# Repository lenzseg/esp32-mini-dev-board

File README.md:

# ESP32-C3 Mini Dev Board

Compact 4-layer ESP32-C3 development board with native USB-C, a 3.3 V LDO, USB ESD/surge protection and breakout headers, designed in KiCad 10 and prepared for JLCPCB fabrication.

## Overview

A small, low-cost breadboard-friendly board for prototyping with the ESP32-C3 (Wi-Fi + BLE, RISC-V). It is a personal design project that covers the full hardware flow: schematic capture, a custom component library with manufacturer part numbers, 4-layer layout with controlled-impedance USB routing, DFM checks and fabrication outputs.

**Design goals**
- Power and program the board over a single USB-C cable (native USB, no USB-UART bridge)
- Protect the USB port against ESD and surge events
- Keep the board small, with the module antenna kept clear of copper
- Use parts that are in stock at the assembly house and pass the fab's DFM rules

## Key specifications

| Item | Value |
|---|---|
| Module | ESP32-C3-WROOM-02 |
| Input power | 5 V via USB-C (also on the 5V header pin) |
| 3.3 V regulator | AP2112K-3.3 LDO |
| USB protection | USBLC6-2SC6 (ESD on data lines), SMAJ5.0A TVS (VBUS) |
| Clocks | 32.768 kHz crystal (FC-135R) for the RTC |
| User controls | BOOT and RST (EN) push buttons |
| Headers | 2 × 8-pin, 2.54 mm (power, UART, GPIO) |
| Board size | 30.6 × 38.0 mm |
| Layers / thickness | 4 layers, 1.6 mm (1.5842 mm calculated stackup) |
| USB differential pair | 90 Ω target, 0.1925 mm trace / 0.18 mm gap (USB net class) |
| EDA | KiCad 10 |
| Revision | 1.0 |

## Design highlights

- **Power entry:** USB-C VBUS passes through a surge TVS (SMAJ5.0A) before the AP2112K-3.3 LDO. Bulk and bypass capacitors (4.7 µF, GRM188Z71C475KE21D) are placed at the regulator and module supply pins.
- **USB protection:** USBLC6-2SC6 on D+/D- for low-capacitance ESD protection, placed close to the connector.
- **Controlled-impedance USB:** D+/D- are routed as a 90 Ω differential pair on the top layer over a solid GND plane (see [PCB layout](#pcb-layout)).
- **Antenna keep-out:** the module's antenna overhangs the board edge, with no copper or components under it.
- **Boot and reset:** BOOT (GPIO9) and EN push buttons with pull-ups and debounce capacitors allow programming without external tools.
- **Manufacturability:** the layout was revised to pass the JLCDFM checks. Copper zones were resized, vias were removed from silkscreen, keep-outs were added around the soldermask-expansion rule bug, headers were moved away from the module to satisfy the THT-SMT spacing rule, and track spacing was increased.
- **Own component library:** symbols in `libs/` carry an IPN and MPN for each part, so the BOM is traceable.

## Pinout

Header pin labels follow the board silkscreen (see the render above). Check them against the schematic before wiring anything.

| Header | Pins (square pad first) |
|---|---|
| Left | 3V3, GND, EN, 4, 5, 6, 7, BOOT |
| Right | 5V, GND, 3, GND, TX, RX, GND, 10 |

Numbers are ESP32-C3 GPIO numbers.

## Schematics

Source files are in [`src/`](src):

- `esp32-mini-dev-board.kicad_sch`: root sheet and index
- `block-diagram.kicad_sch`: system block diagram
- `circuit-design.kicad_sch`: detailed circuit (USB power entry, 3.3 V LDO, module, clock, BOOT/EN, headers)

## PCB layout

| Top | Inner 1 (GND) | Inner 2 (power) | Bottom (mirrored) |
|---|---|---|---|
|  |  |  |  |

## Tools

- KiCad 10.0
- KiCad PCB Calculator (coupled microstrip) for the differential-pair impedance

## Author

Nelson Rodriguez (LENZSEG)

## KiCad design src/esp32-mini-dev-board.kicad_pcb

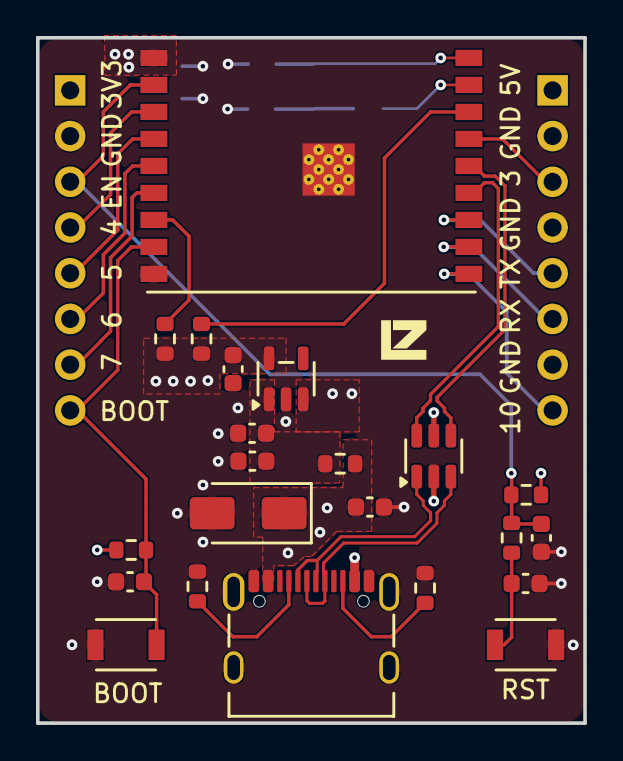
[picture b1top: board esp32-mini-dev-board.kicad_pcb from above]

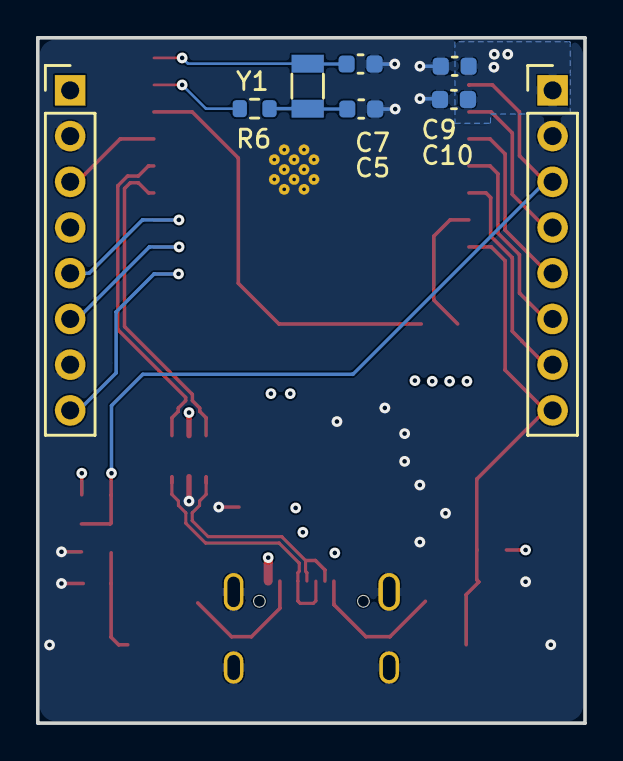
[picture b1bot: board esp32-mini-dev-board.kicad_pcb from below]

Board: 4 copper layers, 30.4 x 38.1 mm, 30 parts (8 on the bottom side), 26 nets.

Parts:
C1, C2, C3, C4, C6, C8, C9, C11: 4.7uF; C_0603_1608Metric
C5, C7, C10: C; C_0603_1608Metric
D1: SMAJ5.0A; D_SMA
J1: USB_C_Receptacle_USB2.0_16P; USB_C_Receptacle_G-Switch_GT-USB-7010ASV
J2, J3: Conn_01x08_Pin; PinHeader_1x08_P2.54mm_Vertical
R1, R2, R3, R4, R5, R6, R7, R8, R9: R; R_0603_1608Metric
SW1, SW2: SW_Push; SW_SPST_B3U-1000P
U1: USBLC6-2SC6; SOT-23-6
U2: AP2112K-3.3; SOT-23-5
U3: ESP32-C3-WROOM-02
Y1: 32.768kHz; Crystal_SMD_3215-2Pin_3.2x1.5mm

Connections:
+3V3: C8.1, C9.1, C10.1, J2.1, R4.1, R7.1, R8.1, R9.1, U2.5 (VOUT), U3.1 (3V3)
+5V: C4.1, C6.1, J3.1, R5.2, U2.1 (VIN), U2.3 (EN)
/CIRCUIT DESIGN/BOOT: C11.1, J2.8, R9.2, SW2.2, U3.8 (IO9)
/CIRCUIT DESIGN/EN: C3.1, J2.3, R3.2, R4.2, U3.2 (EN)
/CIRCUIT DESIGN/IO3: J3.3, U3.15 (IO3)
/CIRCUIT DESIGN/IO4: J2.4, U3.3 (IO4)
/CIRCUIT DESIGN/IO5: J2.5, U3.4 (IO5)
/CIRCUIT DESIGN/IO6: J2.6, U3.5 (IO6)
/CIRCUIT DESIGN/IO7: J2.7, U3.6 (IO7)
/CIRCUIT DESIGN/IO10: J3.8, U3.10 (IO10)
/CIRCUIT DESIGN/RXD: J3.6, U3.11 (IO20/RXD)
/CIRCUIT DESIGN/TXD: J3.5, U3.12 (IO21/TXD)
/CIRCUIT DESIGN/USB_D+: U1.4 (I/O2), U3.14 (IO19)
/CIRCUIT DESIGN/USB_D-: U1.6 (I/O1), U3.13 (IO18)
/CIRCUIT DESIGN/USB_IN+: J1.A6 (D+), J1.B6 (D+), U1.3 (I/O2)
/CIRCUIT DESIGN/USB_IN-: J1.A7 (D-), J1.B7 (D-), U1.1 (I/O1)
/CIRCUIT DESIGN/VBUS: C2.1, D1.1 (A1), J1.A4 (VBUS), J1.A9 (VBUS), J1.B4 (VBUS), J1.B9 (VBUS), R5.1, U1.5 (VBUS)
/CIRCUIT DESIGN/XTAL_32K_N: R6.2, U3.17 (IO1)
/CIRCUIT DESIGN/XTAL_32K_P: C5.1, U3.18 (IO0), Y1.1
GND: C1.2, C2.2, C3.2, C4.2, C5.2, C6.2, C7.2, C8.2, C9.2, C10.2, C11.2, D1.2 (A2), J1.A1 (GND), J1.A12 (GND), J1.B1 (GND), J1.B12 (GND), J1.SH (SHIELD), J2.2, J3.2, J3.4, J3.7, R1.2, R2.2, SW1.1, SW2.1, U1.2 (GND), U2.2 (GND), U3.9 (GND), U3.19 (GND)
unnamed: C1.1, R3.1, SW1.2
unnamed: C7.1, R6.1, Y1.2
unnamed: J1.A5 (CC1), R2.1
unnamed: J1.B5 (CC2), R1.1
unnamed: R7.2, U3.16 (IO2)
unnamed: R8.2, U3.7 (IO8)
